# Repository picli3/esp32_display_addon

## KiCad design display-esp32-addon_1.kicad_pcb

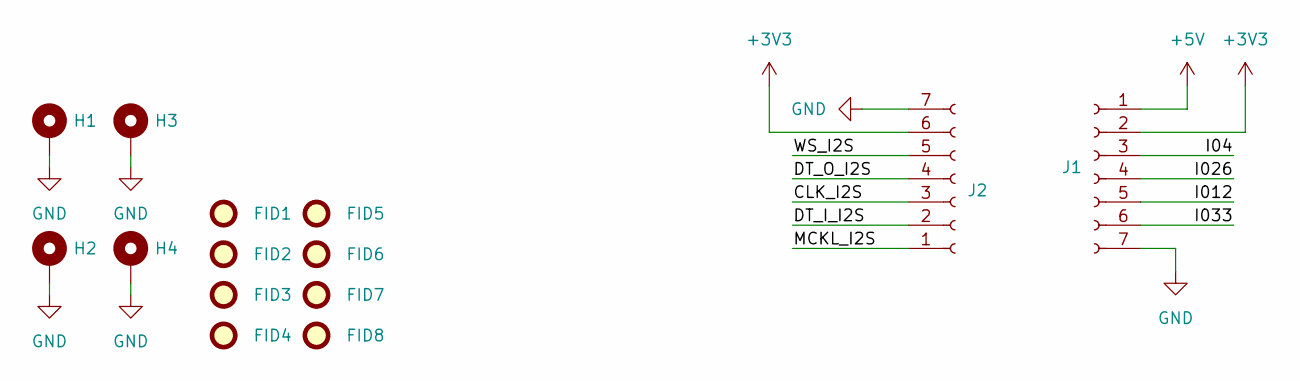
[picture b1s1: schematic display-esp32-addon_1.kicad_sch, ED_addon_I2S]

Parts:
FID1, FID2, FID3, FID4, FID5, FID6, FID7, FID8: Fiducial; Fiducial_1mm_Mask2mm
H1, H2, H3, H4: MountingHole_Pad; MountingHole_3.2mm_M3_DIN965_Pad
J1, J2: Conn_01x07_Socket; PinSocket_1x07_P2.54mm_Vertical; Mfr. Part PM254V-11-07-H85; LCSC Part C2832270

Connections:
+3V3: J1.2, J2.6
+5V: J1.1
/CLK_I2S: J2.3
/DT_I_I2S: J2.2
/DT_O_I2S: J2.4
/I04: J1.3
/I012: J1.5
/I026: J1.4
/I033: J1.6
/MCKL_I2S: J2.1
/WS_I2S: J2.5
GND: H1.1, H2.1, H3.1, H4.1, J1.7, J2.7

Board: 2 copper layers, 14 parts (4 on the bottom side), 2 nets, no tracks yet.

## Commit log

2023-10-29 plantilla completada
2023-10-30 agregando numero de parte a los conectores principales
2023-11-02 agregando fiducials
